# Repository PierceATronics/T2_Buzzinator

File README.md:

# T2_Buzzinator
T2 Buzzinator - Programmable Timed Buzzer

The T2 Buzzinator is an adjustable timed buzzer circuit emitting noise from a magnetic transducer buzzer for a programmable duration of time. The buzz time duration is programmed simply by a potentiometer and swtich.  The T2 Buzzinator is built around two 555 Timer ICs and other discrete components.

This repo contains the KiCAD schematic and PCB design of the Buzzinator, as well as other supporting documents (Bill of Materials (BOM), LTSpice simulation, etc.)

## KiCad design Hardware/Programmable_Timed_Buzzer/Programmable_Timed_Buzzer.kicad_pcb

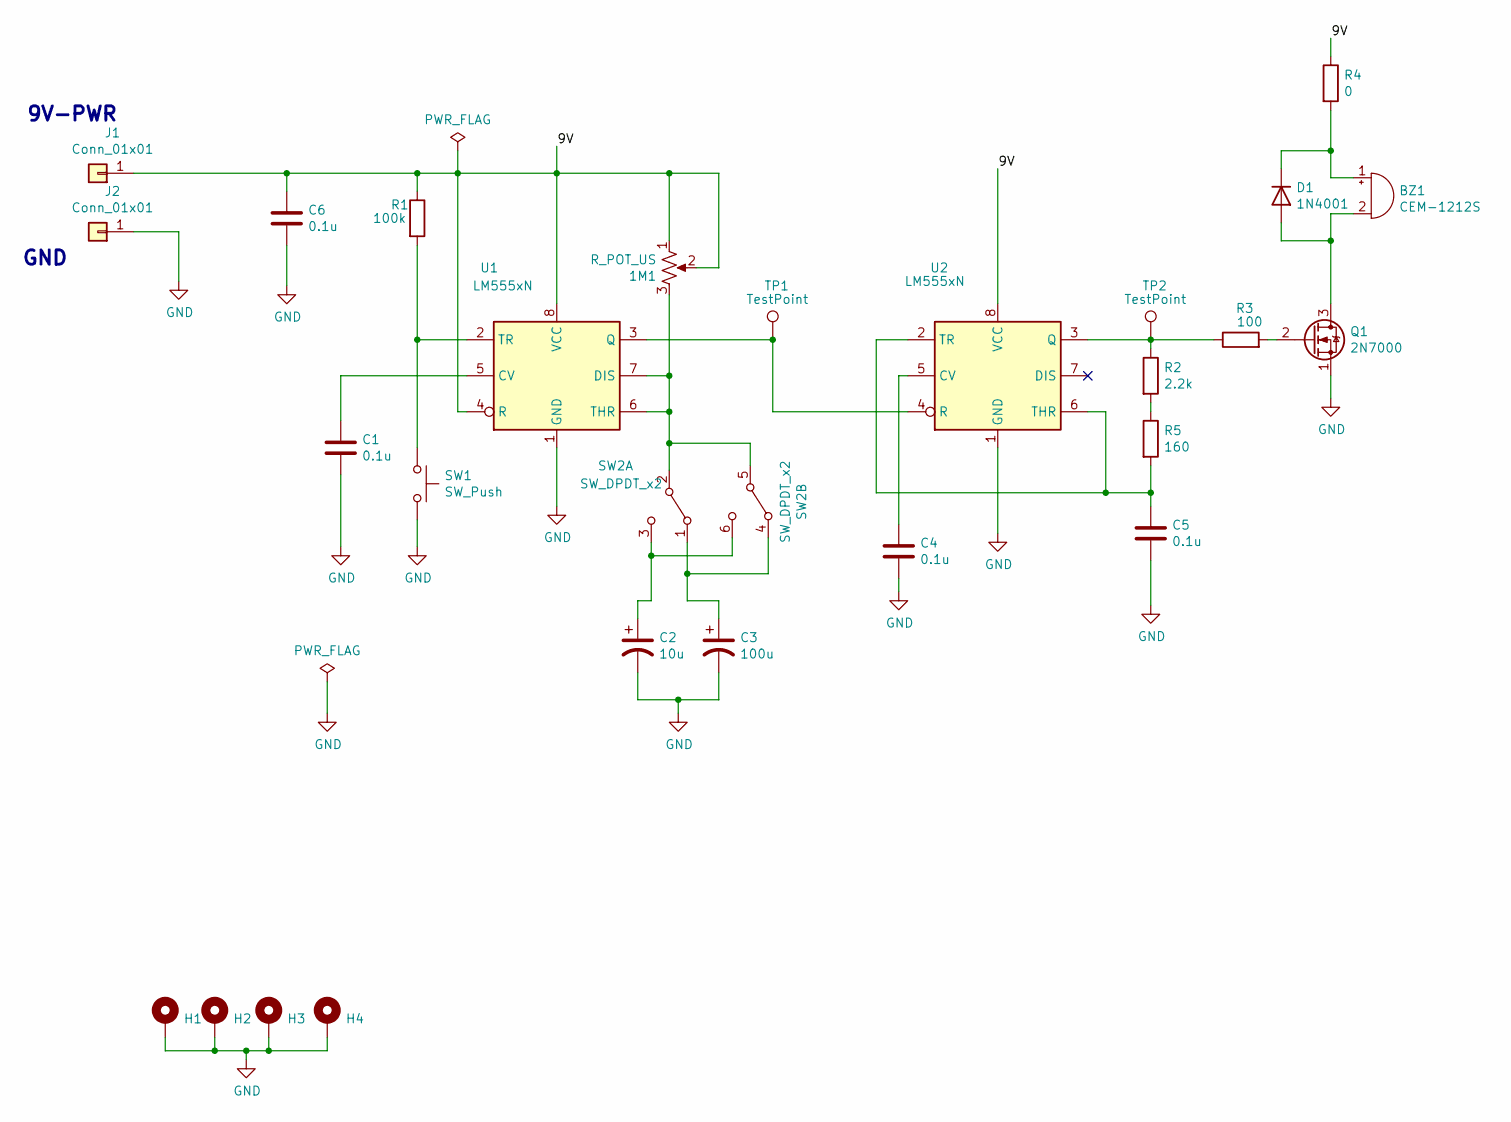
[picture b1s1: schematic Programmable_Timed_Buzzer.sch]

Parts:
1M1: R_POT_US; Potentiometer_Bourns_3386F_Vertical
BZ1: CEM-1212S; MagneticBuzzer_ProSignal_ABT-410-RC
C1, C4, C5, C6: 0.1u; C_Axial_L5.1mm_D3.1mm_P7.50mm_Horizontal
C2: 10u; CP_Radial_D5.0mm_P2.50mm
C3: 100u; CP_Radial_D8.0mm_P3.50mm
D1: 1N4001; D_DO-41_SOD81_P10.16mm_Horizontal
H1, H2, H3, H4: MountingHole_Pad; MountingHole_3.7mm_Pad
J1, J2: Conn_01x01; PinHeader_1x01_P2.54mm_Vertical
Q1: 2N7000; TO-92L_Wide
R1: 100k; R_Axial_DIN0207_L6.3mm_D2.5mm_P10.16mm_Horizontal
R2: 2.2k; R_Axial_DIN0207_L6.3mm_D2.5mm_P10.16mm_Horizontal
R3: 100; R_Axial_DIN0207_L6.3mm_D2.5mm_P10.16mm_Horizontal
R4: 0; R_Axial_DIN0207_L6.3mm_D2.5mm_P10.16mm_Horizontal
R5: 160; R_Axial_DIN0207_L6.3mm_D2.5mm_P10.16mm_Horizontal
SW1: SW_Push; SW_PUSH_6mm_H13mm
SW2: SW_DPDT_x2; SW_CuK_JS202011CQN_DPDT_Straight
TP1, TP2: TestPoint; Pin_D1.3mm_L11.0mm
U1, U2: LM555xN; DIP-8_W7.62mm

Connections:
/9V: 1M1.1, 1M1.2, C6.1, J1.1, R1.1, R4.1, U1.4 (R), U1.8 (VCC), U2.8 (VCC)
GND: C1.2, C2.2, C3.2, C4.2, C5.2, C6.2, H1.1, H2.1, H3.1, H4.1, J2.1, Q1.1 (S), SW1.2, U1.1 (GND), U2.1 (GND)
unnamed: 1M1.3, SW2.2 (B), SW2.5 (B), U1.6 (THR), U1.7 (DIS)
unnamed: BZ1.1 (-), D1.1 (K), R4.2
unnamed: BZ1.2 (+), D1.2 (A), Q1.3 (D)
unnamed: C1.1, U1.5 (CV)
unnamed: C2.1, SW2.3 (C), SW2.6 (C)
unnamed: C3.1, SW2.1 (A), SW2.4 (A)
unnamed: C4.1, U2.5 (CV)
unnamed: C5.1, R5.2, U2.2 (TR), U2.6 (THR)
unnamed: Q1.2 (G), R3.2
unnamed: R1.2, SW1.1, U1.2 (TR)
unnamed: R2.1, R3.1, TP2.1, U2.3 (Q)
unnamed: R2.2, R5.1
unnamed: TP1.1, U1.3 (Q), U2.4 (R)

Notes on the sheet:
9V-PWR
GND

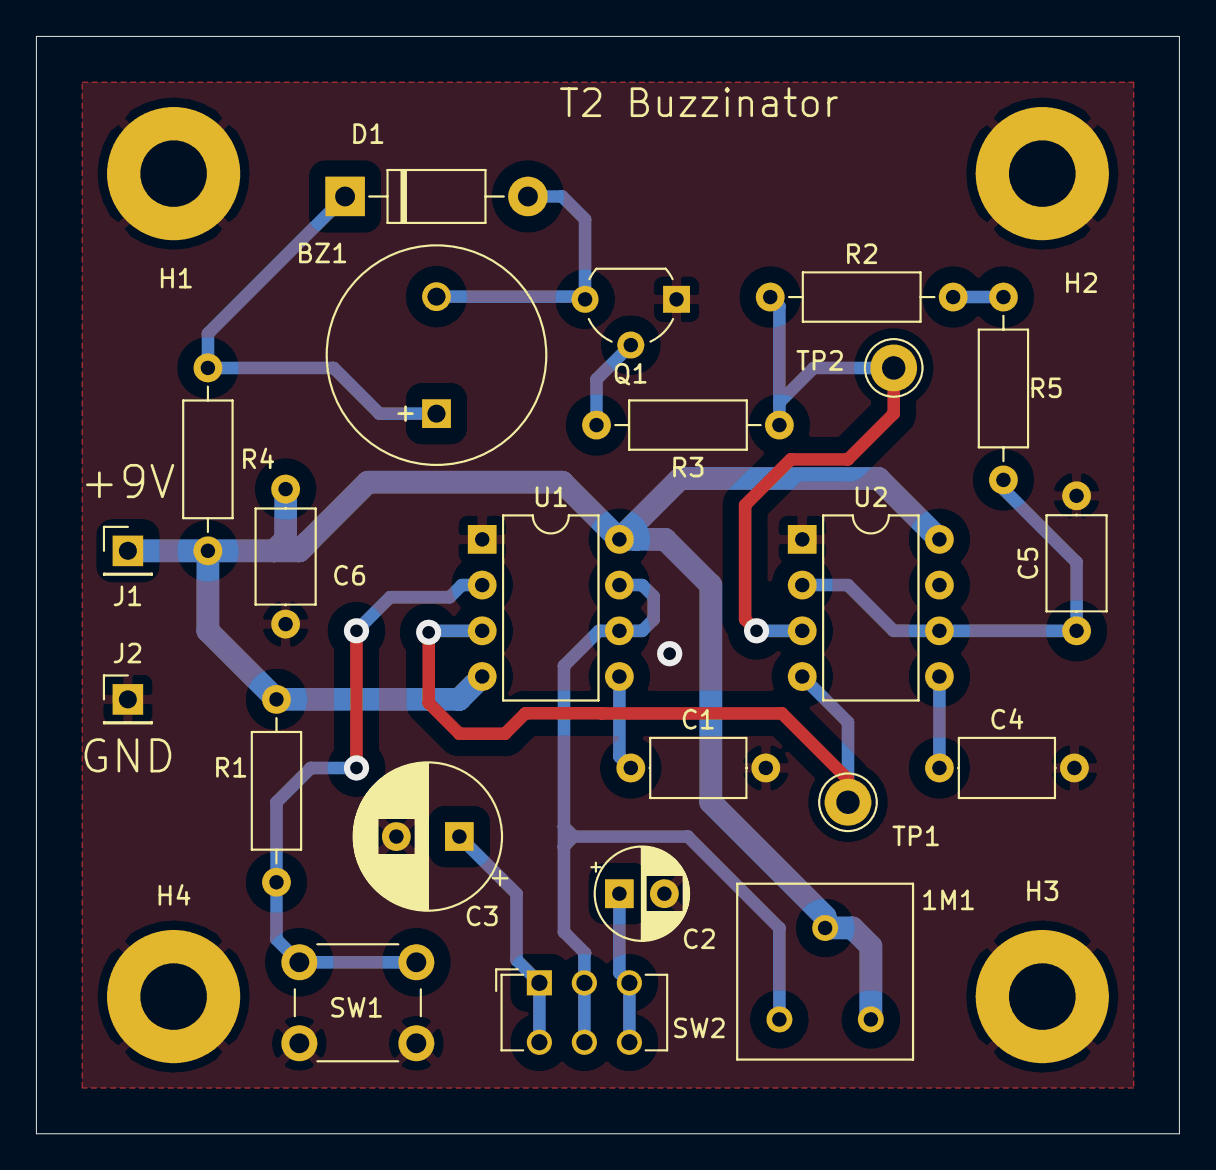
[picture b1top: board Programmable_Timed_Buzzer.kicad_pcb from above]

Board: 2 copper layers, 63.5 x 61.0 mm, 27 parts (0 on the bottom side), 15 nets.

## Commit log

2020-10-05 First commit of the T2 Buzzinator PCB design.
2020-10-05 Added the System Block Diagram to Documents folder.
2020-10-05 Renamed the Simulation folder to LTSpice_Simulation.
2020-10-05 Create LICENSE
